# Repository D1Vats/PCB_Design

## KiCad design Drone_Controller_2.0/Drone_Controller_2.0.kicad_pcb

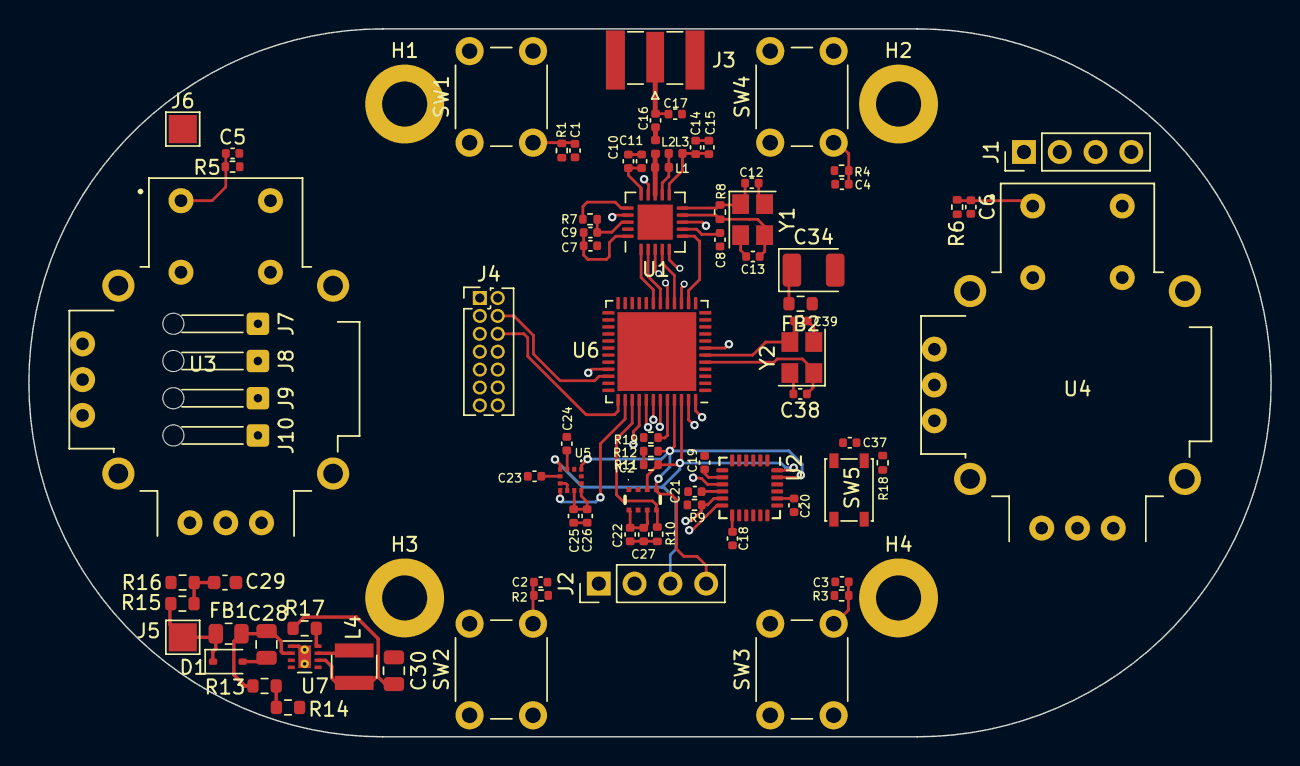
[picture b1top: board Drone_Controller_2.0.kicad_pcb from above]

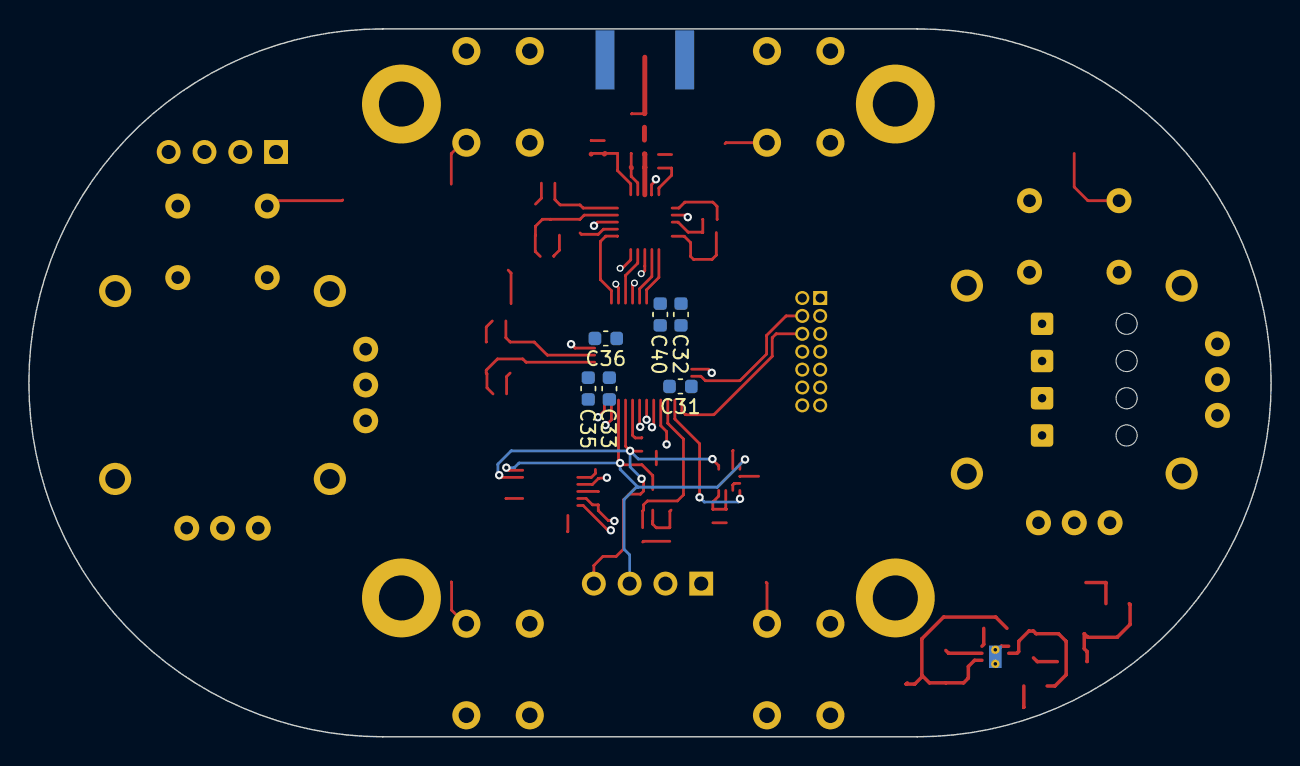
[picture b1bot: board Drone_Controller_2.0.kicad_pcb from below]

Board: 4 copper layers, 88.2 x 50.2 mm, 95 parts (6 on the bottom side), 57 nets.

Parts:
C1, C2, C3, C4, C5, C6: 0.1uf; C_0402_1005Metric
C7: 33nf; C_0402_1005Metric
C8, C24: 10uf; C_0402_1005Metric
C9, C10, C11, C18: 10nf; C_0402_1005Metric
C12, C13, C38, C39: 12pf; C_0402_1005Metric
C14, C20: 2.2nf; C_0402_1005Metric
C15: 4.7p; C_0402_1005Metric
C16: 1p5; C_0402_1005Metric
C17: 1p; C_0402_1005Metric
C19, C21, C22, C25, C26, C27, C37: 100nf; C_0402_1005Metric
C23: 220nf; C_0402_1005Metric
C28: 10uf; C_0805_2012Metric
C29, C36: 10nf; C_0603_1608Metric
C30: 22uf; C_0805_2012Metric
C31, C32, C33: 100nf; C_0603_1608Metric
C34: 1uf; CP_EIA-3528-21_Kemet-B
C35, C40: 4.7uf; C_0603_1608Metric
D1: SD24_SOD323; D_SOD-323
FB1: 120R; R_0805_2012Metric
FB2: 600R@100MHz; R_0603_1608Metric
H1, H2, H3, H4: MountingHole; MountingHole_3.2mm_M3_DIN965_Pad
IC2: DPS310XTSA1
J1, J2: Conn_01x04; PinHeader_1x04_P2.54mm_Vertical
J3: Conn_Coaxial; SMA_Samtec_SMA-J-P-X-ST-EM1_EdgeMount
J4: Conn_ST_STDC14; PinHeader_2x07_P1.27mm_Vertical
J5: V+; TestPoint_Pad_2.0x2.0mm
J6: V-; TestPoint_Pad_2.0x2.0mm
J7, J8, J9, J10: Conn_01x01_Pin; SolderWire-0.1sqmm_1x01_D0.4mm_OD1mm_Relief
L1: 8.2nH; L_0402_1005Metric
L2: 3.9nH; L_0402_1005Metric
L3: 2.7nH; L_0402_1005Metric
L4: VLS252010HBX-2R2M-1; L_Abracon_ASPI-3012S
R1, R2, R3, R4, R5, R6: 3.3k; R_0402_1005Metric
R7: 22k; R_0402_1005Metric
R8: 1M; R_0402_1005Metric
R9: 1k; R_0402_1005Metric
R10: 51k; R_0402_1005Metric
R11, R12: 4.7k; R_0402_1005Metric
R13: 110k; R_0603_1608Metric
R14: 12k; R_0603_1608Metric
R15: 4.7k; R_0603_1608Metric
R16: 1.2k; R_0603_1608Metric
R17: 100k; R_0603_1608Metric
R18, R19: 10k; R_0402_1005Metric
SW1, SW2, SW3, SW4: SW_Push; SW_PUSH_6mm_H4.3mm
SW5: SW_Push; SW_SPST_PTS810
U1: NRF24L01; QFN-20-1EP_4x4mm_P0.5mm_EP2.5x2.5mm
U2: MPU-6050; InvenSense_QFN-24_4x4mm_P0.5mm
U3, U4: COM-09032; XDCR_COM-09032
U5: IIS2MDCTR
U6: STM32F411CEUx; QFN-48-1EP_7x7mm_P0.5mm_EP5.6x5.6mm
U7: TPS62162DSG; WSON-8-1EP_2x2mm_P0.5mm_EP0.9x1.6mm_ThermalVias
Y1, Y2: 16MHz; Crystal_SMD_3225-4Pin_3.2x2.5mm

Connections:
C1: C23.1, U5.5 (C1)
DPS_INT: IC2.5 (SDO), R10.2, U6.39 (PB3)
EN: R13.2, R14.1, U7.3 (EN)
FSYNC: R9.1, U2.11 (FSYNC), U6.41 (PB5)
Filter_V_IN: C28.1, FB1.2, R13.1, U7.2 (VIN)
INT/DRDY: U5.7 (INT/DRDY), U6.38 (PA15)
J_SW1: C5.1, R5.2, U3.B1A (SEL+), U6.25 (PB12)
J_SW2: C6.1, R6.2, U4.B1A (SEL+), U6.10 (PA0)
MPU_I2C_SCL: IC2.4 (SCK), J2.4, R12.2, U2.23 (SCL), U5.1 (SCL/SPC), U6.45 (PB8)
MPU_I2C_SDA: IC2.3 (SDI), J2.3, R11.2, U2.24 (SDA), U5.4 (SDA/SDI/SDO), U6.46 (PB9)
MPU_INT: U2.12 (INT), U6.40 (PB4)
Motor_1: J7.1, U6.29 (PA8)
Motor_2: J8.1, U6.30 (PA9)
Motor_3: J9.1, U6.31 (PA10)
Motor_4: J10.1, U6.32 (PA11)
NRF_!CS: U1.2 (CSN), U6.18 (PB0)
NRF_ANT1: L1.2, L3.2, U1.12 (ANT1)
NRF_ANT2: L1.1, L2.1, U1.13 (ANT2)
NRF_CE: U1.1 (CE), U6.19 (PB1)
NRF_IRQ: U1.6 (IRQ), U6.14 (PA4)
NRF_MISO: U1.5 (MISO), U6.17 (PA7)
NRF_MOSI: U1.4 (MOSI), U6.16 (PA6)
NRF_SCK: U1.3 (SCK), U6.15 (PA5)
NRF_VDD_PA: C14.2, C15.2, L3.1, U1.11 (VDD_PA)
NRF_XC1: C12.1, R8.1, U1.10 (XC1), Y1.1
NRF_XC2: C13.1, R8.2, U1.9 (XC2), Y1.3
NRST: C37.1, J4.12 (~RST), R18.2, SW5.2, U6.7 (NRST)
unnamed: C16.1, L2.2
unnamed: C16.2, C17.2, J3.1 (In)
unnamed: C7.1, U1.19 (DVDD)
unnamed: R7.1, U1.16 (IREF)
unnamed: C20.1, U2.20 (CPOUT)
unnamed: C21.1, U2.10 (REGOUT)
unnamed: R19.2, U6.44 (BOOT0)
unnamed: C40.1, U6.22 (VCAP1)
unnamed: L4.1, U7.7 (SW)
PG: R17.2, U7.8 (PG)
RCC_OSC_IN: C38.1, U6.5 (PH0), Y2.1
RCC_OSC_OUT: C39.1, U6.6 (PH1), Y2.3
STM_VDD: C8.1, C9.1, C10.1, C11.1, C18.1, C19.1, C22.1, C24.1, C25.1, C26.1, C27.1, C30.1, C31.1, C32.1, C33.1, C35.1, FB2.1, IC2.6 (VDDIO), IC2.8 (VDD), J1.1, J2.1, J4.3 (VCC), L4.2, R1.1, R2.1, R3.1, R4.1, R5.1, R6.1, R7.2, R11.1, R12.1, R17.1, R18.1, U1.7 (VDD), U1.15 (VDD), U1.18 (VDD), U2.8 (VLOGIC), U2.13 (VDD), U3.H1 (H+), U3.V1 (V+), U4.H1 (H+), U4.V1 (V+), U5.3 (CS), U5.9 (VDD), U5.10 (VDD_IO), U6.1 (VBAT), U6.24 (VDD), U6.36 (VDD), U6.48 (VDD), U7.6 (VOS)
STM_VSS: C1.2, C2.2, C3.2, C4.2, C5.2, C6.2, C7.2, C8.2, C9.2, C10.2, C11.2, C12.2, C13.2, C14.1, C15.1, C17.1, C18.2, C19.2, C20.2, C21.2, C22.2, C23.2, C24.2, C25.2, C26.2, C27.2, C28.2, C29.2, C30.2, C31.2, C32.2, C33.2, C34.2, C35.2, C36.2, C37.2, C38.2, C39.2, C40.2, D1.2 (A2), IC2.1 (GND_1), IC2.7 (GND_2), J1.4, J2.2, J3.2 (Ext), J4.5 (GND), J4.7 (GND), J4.11 (GNDDetect), J6.1, R9.2, R10.1, R14.2, R16.2, R19.1, SW1.1, SW2.1, SW3.1, SW4.1, SW5.1, U1.8 (VSS), U1.14 (VSS), U1.17 (VSS), U1.20 (VSS), U2.1 (CLKIN), U2.9 (AD0), U2.18 (GND), U3.B2A (SEL-), U3.H3 (H-), U3.V3 (V-), U4.B2A (SEL-), U4.H3 (H-), U4.V3 (V-), U5.6 (GND_1), U5.8 (GND_2), U6.8 (VSSA), U6.23 (VSS), U6.35 (VSS), U6.47 (VSS), U6.49 (VSS), U7.1 (PGND), U7.4 (AGND), U7.5 (FB), U7.9 (PAD), Y1.2, Y1.4, Y2.2, Y2.4
SWCLK: J4.6 (JCLK/SWCLK), U6.37 (PA14)
SWDIO: J4.4 (JTMS/SWDIO), U6.34 (PA13)
SW_1: C1.1, R1.2, SW1.2, U6.21 (PB10)
SW_2: C2.1, R2.2, SW2.2, U6.33 (PA12)
SW_3: C3.1, R3.2, SW3.2, U6.2 (PC13)
SW_4: C4.1, R4.2, SW4.2, U6.11 (PA1)
USART1_RX: J4.13 (VCP_RX), U6.43 (PB7)
USART1_TX: J4.14 (VCP_TX), U6.42 (PB6)
USART2_RX: J1.2, U6.13 (PA3)
USART2_TX: J1.3, U6.12 (PA2)
VDDA: C34.1, C36.1, FB2.2, U6.9 (VDDA)
V_IN: D1.1 (A1), FB1.1, J5.1, R15.1
V_IN_Sense: C29.1, R15.2, R16.1, U6.28 (PB15)
X_2_AXIS: U4.H2 (H), U6.3 (PC14)
Y_1_AXIS: U3.V2 (V), U6.26 (PB13), U6.27 (PB14)
Y_2_AXIS: U4.V2 (V), U6.4 (PC15)

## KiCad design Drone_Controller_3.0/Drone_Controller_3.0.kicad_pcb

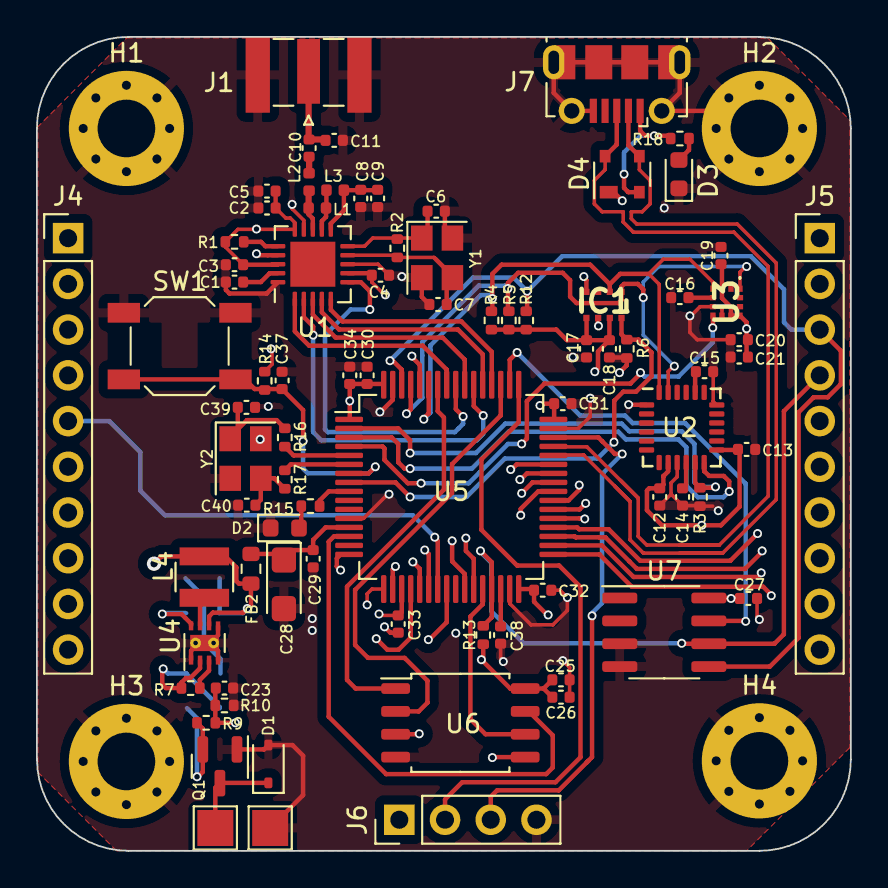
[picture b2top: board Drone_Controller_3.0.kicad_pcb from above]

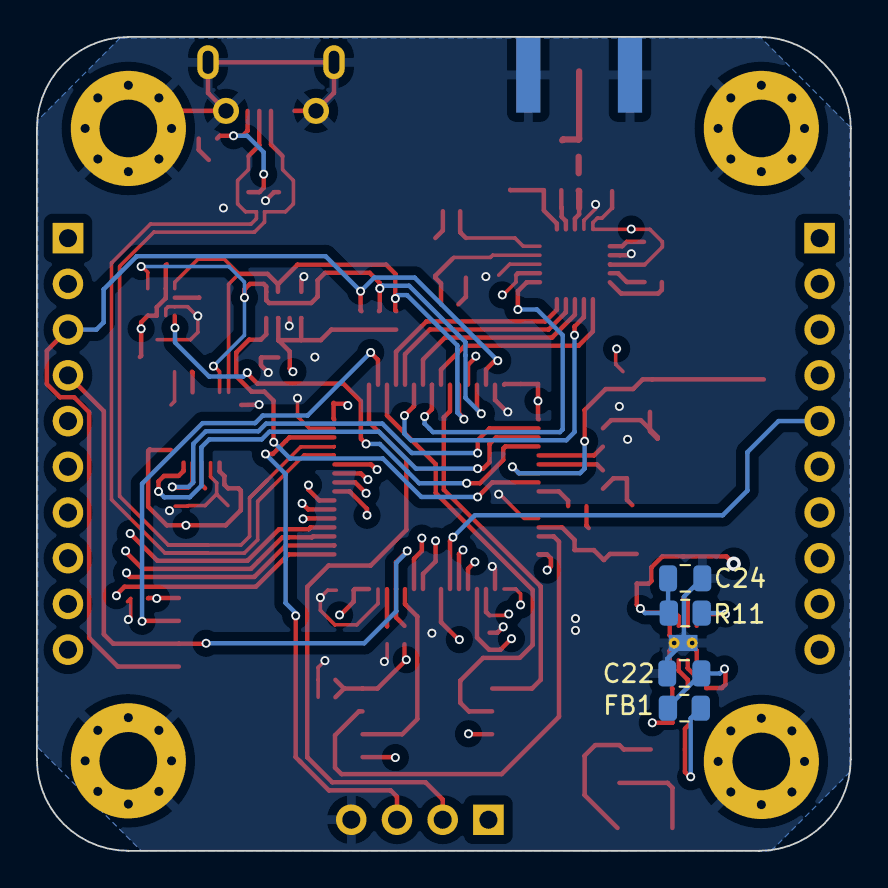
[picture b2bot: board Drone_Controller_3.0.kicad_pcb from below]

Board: 4 copper layers, 45.2 x 45.2 mm, 88 parts (4 on the bottom side), 75 nets.

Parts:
C1: 33nf; C_0402_1005Metric
C2, C19: 10uf; C_0402_1005Metric
C3, C4, C5, C12, C23, C29: 10nf; C_0402_1005Metric
C6, C7, C39, C40: 12pf; C_0402_1005Metric
C8, C15: 2.2nf; C_0402_1005Metric
C9: 4.7p; C_0402_1005Metric
C10: 1p5; C_0402_1005Metric
C11: 1p; C_0402_1005Metric
C13, C14, C17, C18, C20, C21, C30, C31, C32, C33, C37: 100nf; C_0402_1005Metric
C16: 220nf; C_0402_1005Metric
C22: 10uf; C_0805_2012Metric
C24: 22uf; C_0805_2012Metric
C25, C26, C27: 0.1uf; C_0402_1005Metric
C28: 1uf; CP_EIA-3216-18_Kemet-A
C34: 4.7uf; C_0402_1005Metric
C38: 2.2uf; C_0402_1005Metric
D1: SD24_SOD323; D_SOD-323
D2: Green_LED; LED_0603_1608Metric
D3: LED; LED_0603_1608Metric
D4: SP0503BAHT; SOT-143
FB1: 120R; R_0805_2012Metric
FB2: 600R@100MHz; R_0603_1608Metric
H1, H2, H3, H4: MountingHole_Pad; MountingHole_3.2mm_M3_Pad_Via
IC1: DPS310XTSA1
J1: Conn_Coaxial; SMA_Samtec_SMA-J-P-X-ST-EM1_EdgeMount
J2: V+; TestPoint_Pad_2.0x2.0mm
J3: V-; TestPoint_Pad_2.0x2.0mm
J4, J5: Conn_01x10; PinHeader_1x10_P2.54mm_Vertical
J6: Conn_01x04; PinHeader_1x04_P2.54mm_Vertical
J7: USB_B_Micro; USB_Micro-B_Molex-105017-0001
L1: 8.2nH; L_0402_1005Metric
L2: 3.9nH; L_0402_1005Metric
L3: 2.7nH; L_0402_1005Metric
L4: VLS252010HBX-2R2M-1; L_Abracon_ASPI-3012S
Q1: Si2319CDS; SOT-23
R1: 22k; R_0402_1005Metric
R2: 1M; R_0402_1005Metric
R3, R15: 1k; R_0402_1005Metric
R4, R5, R12, R13: 4.7k; R_0402_1005Metric
R6: 51k; R_0402_1005Metric
R7: 110k; R_0402_1005Metric
R9: 47k; R_0402_1005Metric
R10: 12k; R_0402_1005Metric
R11: 100k; R_0805_2012Metric
R14: 10k; R_0402_1005Metric
R16, R17: 0R; R_0402_1005Metric
R18: 2.2k; R_0402_1005Metric
SW1: SW_Push; SW_SPST_SKQG_WithStem
U1: NRF24L01; QFN-20-1EP_4x4mm_P0.5mm_EP2.5x2.5mm
U2: MPU-6050; InvenSense_QFN-24_4x4mm_P0.5mm
U3: IIS2MDCTR
U4: TPS62162DSG; WSON-8-1EP_2x2mm_P0.5mm_EP0.9x1.6mm_ThermalVias
U5: STM32F412RGTx; LQFP-64_10x10mm_P0.5mm
U6: W25Q32JVSS; SOIC-8_5.23x5.23mm_P1.27mm
U7: AT24CS08-SSHM; SOIC-8_3.9x4.9mm_P1.27mm
Y1, Y2: 16MHz; Crystal_SMD_3225-4Pin_3.2x2.5mm

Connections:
3.3V: C2.1, C3.1, C4.1, C5.1, C12.1, C13.1, C17.1, C18.1, C19.1, C20.1, C21.1, C24.1, C25.1, C26.1, C27.1, C30.1, C31.1, C32.1, C33.1, C34.1, FB2.1, IC1.6 (VDDIO), IC1.8 (VDD), J6.1, L4.2, R1.2, R4.1, R5.1, R11.1, R12.1, R13.1, R14.1, U1.7 (VDD), U1.15 (VDD), U1.18 (VDD), U2.8 (VLOGIC), U2.13 (VDD), U3.3 (CS), U3.9 (VDD), U3.10 (VDD_IO), U4.6 (VOS), U5.1 (VBAT), U5.19 (VDD), U5.32 (VDD), U5.48 (VDD), U5.64 (VDD), U6.8 (VCC), U7.8 (VCC)
BOOT0: J4.1, U5.60 (BOOT0)
C1: C16.1, U3.5 (C1)
D+: D4.4 (K), J7.3 (D+), U5.45 (PA12)
D-: D4.3 (K), J7.2 (D-), U5.44 (PA11)
DPS_INT: IC1.5 (SDO), R6.2, U5.8 (PC0)
EEPROM_SCL: J5.4, R13.2, U5.29 (PB10), U7.6 (SCL)
EEPROM_SDA: J5.3, R12.2, U5.62 (PB9), U7.5 (SDA)
EEPROM_WP: U5.50 (PA15), U7.7 (WP)
EN: R7.2, U4.3 (EN)
FLASH_CLK: U5.28 (PB2), U6.6 (CLK)
FLASH_CS: U5.58 (PB6), U6.1 (~CS)
FLASH_IO0: U5.40 (PC9), U6.5 (DI(IO0))
FLASH_IO1: U5.51 (PC10), U6.2 (DO(IO1))
FLASH_IO2: U5.39 (PC8), U6.3 (IO2)
FLASH_IO3: U5.14 (PA0), U6.7 (IO3)
FSYNC: R3.1, U2.11 (FSYNC), U5.2 (PC13)
Filter_V_IN: C22.1, FB1.2, R7.1, U4.2 (VIN)
GND: C1.2, C2.2, C3.2, C4.2, C5.2, C6.2, C7.2, C8.1, C9.1, C11.1, C12.2, C13.2, C14.2, C15.2, C16.2, C17.2, C18.2, C19.2, C20.2, C21.2, C22.2, C23.2, C24.2, C25.2, C26.2, C27.2, C28.2, C29.2, C30.2, C31.2, C32.2, C33.2, C34.2, C37.2, C38.2, C39.2, C40.2, D1.2 (A2), D2.1 (K), D3.1 (K), D4.1 (A), H1.1, H2.1, H3.1, H4.1, IC1.1 (GND_1), IC1.7 (GND_2), J1.2 (Ext), J3.1, J6.4, J7.5 (GND), J7.6 (Shield), Q1.1 (G), R3.2, R6.1, R10.2, SW1.1, U1.8 (VSS), U1.14 (VSS), U1.17 (VSS), U1.20 (VSS), U2.1 (CLKIN), U2.9 (AD0), U2.18 (GND), U3.6 (GND_1), U3.8 (GND_2), U4.1 (PGND), U4.4 (AGND), U4.5 (FB), U4.9 (PAD), U5.12 (VSSA), U5.18 (VSS), U5.31 (VSS), U5.47 (VSS), U5.63 (VSS), U6.4 (GND), U7.3 (A2), U7.4 (GND), Y1.2, Y1.4, Y2.2, Y2.4
INT/DRDY: U3.7 (INT/DRDY), U5.4 (PC15)
MPU_I2C_SCL: IC1.4 (SCK), R5.2, U2.23 (SCL), U3.1 (SCL/SPC), U5.61 (PB8)
MPU_I2C_SDA: IC1.3 (SDI), R4.2, U2.24 (SDA), U3.4 (SDA/SDI/SDO), U5.59 (PB7)
MPU_INT: U2.12 (INT), U5.3 (PC14)
NRF_!CS: U1.2 (CSN), U5.54 (PD2)
NRF_ANT1: L1.2, L3.2, U1.12 (ANT1)
NRF_ANT2: L1.1, L2.1, U1.13 (ANT2)
NRF_CE: U1.1 (CE), U5.57 (PB5)
NRF_IRQ: U1.6 (IRQ), U5.56 (PB4)
NRF_MISO: U1.5 (MISO), U5.52 (PC11)
NRF_MOSI: U1.4 (MOSI), U5.53 (PC12)
NRF_SCK: U1.3 (SCK), U5.55 (PB3)
NRF_VDD_PA: C8.2, C9.2, L3.1, U1.11 (VDD_PA)
NRF_XC1: C6.1, R2.1, U1.10 (XC1), Y1.1
NRF_XC2: C7.1, R2.2, U1.9 (XC2), Y1.3
NRST: C37.1, R14.2, SW1.2, U5.7 (NRST)
unnamed: C10.1, L2.2
unnamed: C39.1, R16.2, Y2.1
unnamed: C40.1, R17.1, Y2.3
unnamed: D1.1 (A1), J2.1, Q1.3 (D)
unnamed: D2.2 (A), R15.2
unnamed: D3.2 (A), R18.1
unnamed: C10.2, C11.2, J1.1 (In)
unnamed: C1.1, U1.19 (DVDD)
unnamed: R1.1, U1.16 (IREF)
unnamed: C15.1, U2.20 (CPOUT)
unnamed: C14.1, U2.10 (REGOUT)
unnamed: L4.1, U4.7 (SW)
unnamed: C38.1, U5.30 (VCAP_1)
PA4: J4.8, U5.20 (PA4)
PA5: J4.7, U5.21 (PA5)
PA8: J4.4, U5.41 (PA8)
PA9: J4.3, U5.42 (PA9)
PA10: J4.2, U5.43 (PA10)
PC6: J5.2, U5.37 (PC6)
PC7: J5.1, U5.38 (PC7)
PG: R11.2, U4.8 (PG)
PWM_1: J4.6, U5.22 (PA6)
PWM_2: J4.5, U5.23 (PA7)
PWM_3: J5.5, U5.26 (PB0)
PWM_4: J5.6, U5.27 (PB1)
RCC_OSC_IN: R16.1, U5.5 (PH0)
RCC_OSC_OUT: R17.2, U5.6 (PH1)
SPI2_MISO: J5.8, U5.35 (PB14)
SPI2_MOSI: J5.7, U5.36 (PB15)
SPI2_NSS: J5.10, U5.33 (PB12)
SPI2_SCK: J5.9, U5.34 (PB13)
SYS_SWCLK: J6.2, U5.49 (PA14)
SYS_SWDIO: J6.3, U5.46 (PA13)
Test_LED: R15.1, U5.9 (PC1)
UART_RX: J4.10, U5.17 (PA3)
UART_TX: J4.9, U5.16 (PA2)
VBUS: D4.2 (K), J7.1 (VBUS), R18.2
VDDA: C28.1, C29.1, FB2.2, U5.13 (VDDA)
V_IN: FB1.1, Q1.2 (S), R9.1
V_IN_Sense: C23.1, R9.2, R10.1, U5.24 (PC4)

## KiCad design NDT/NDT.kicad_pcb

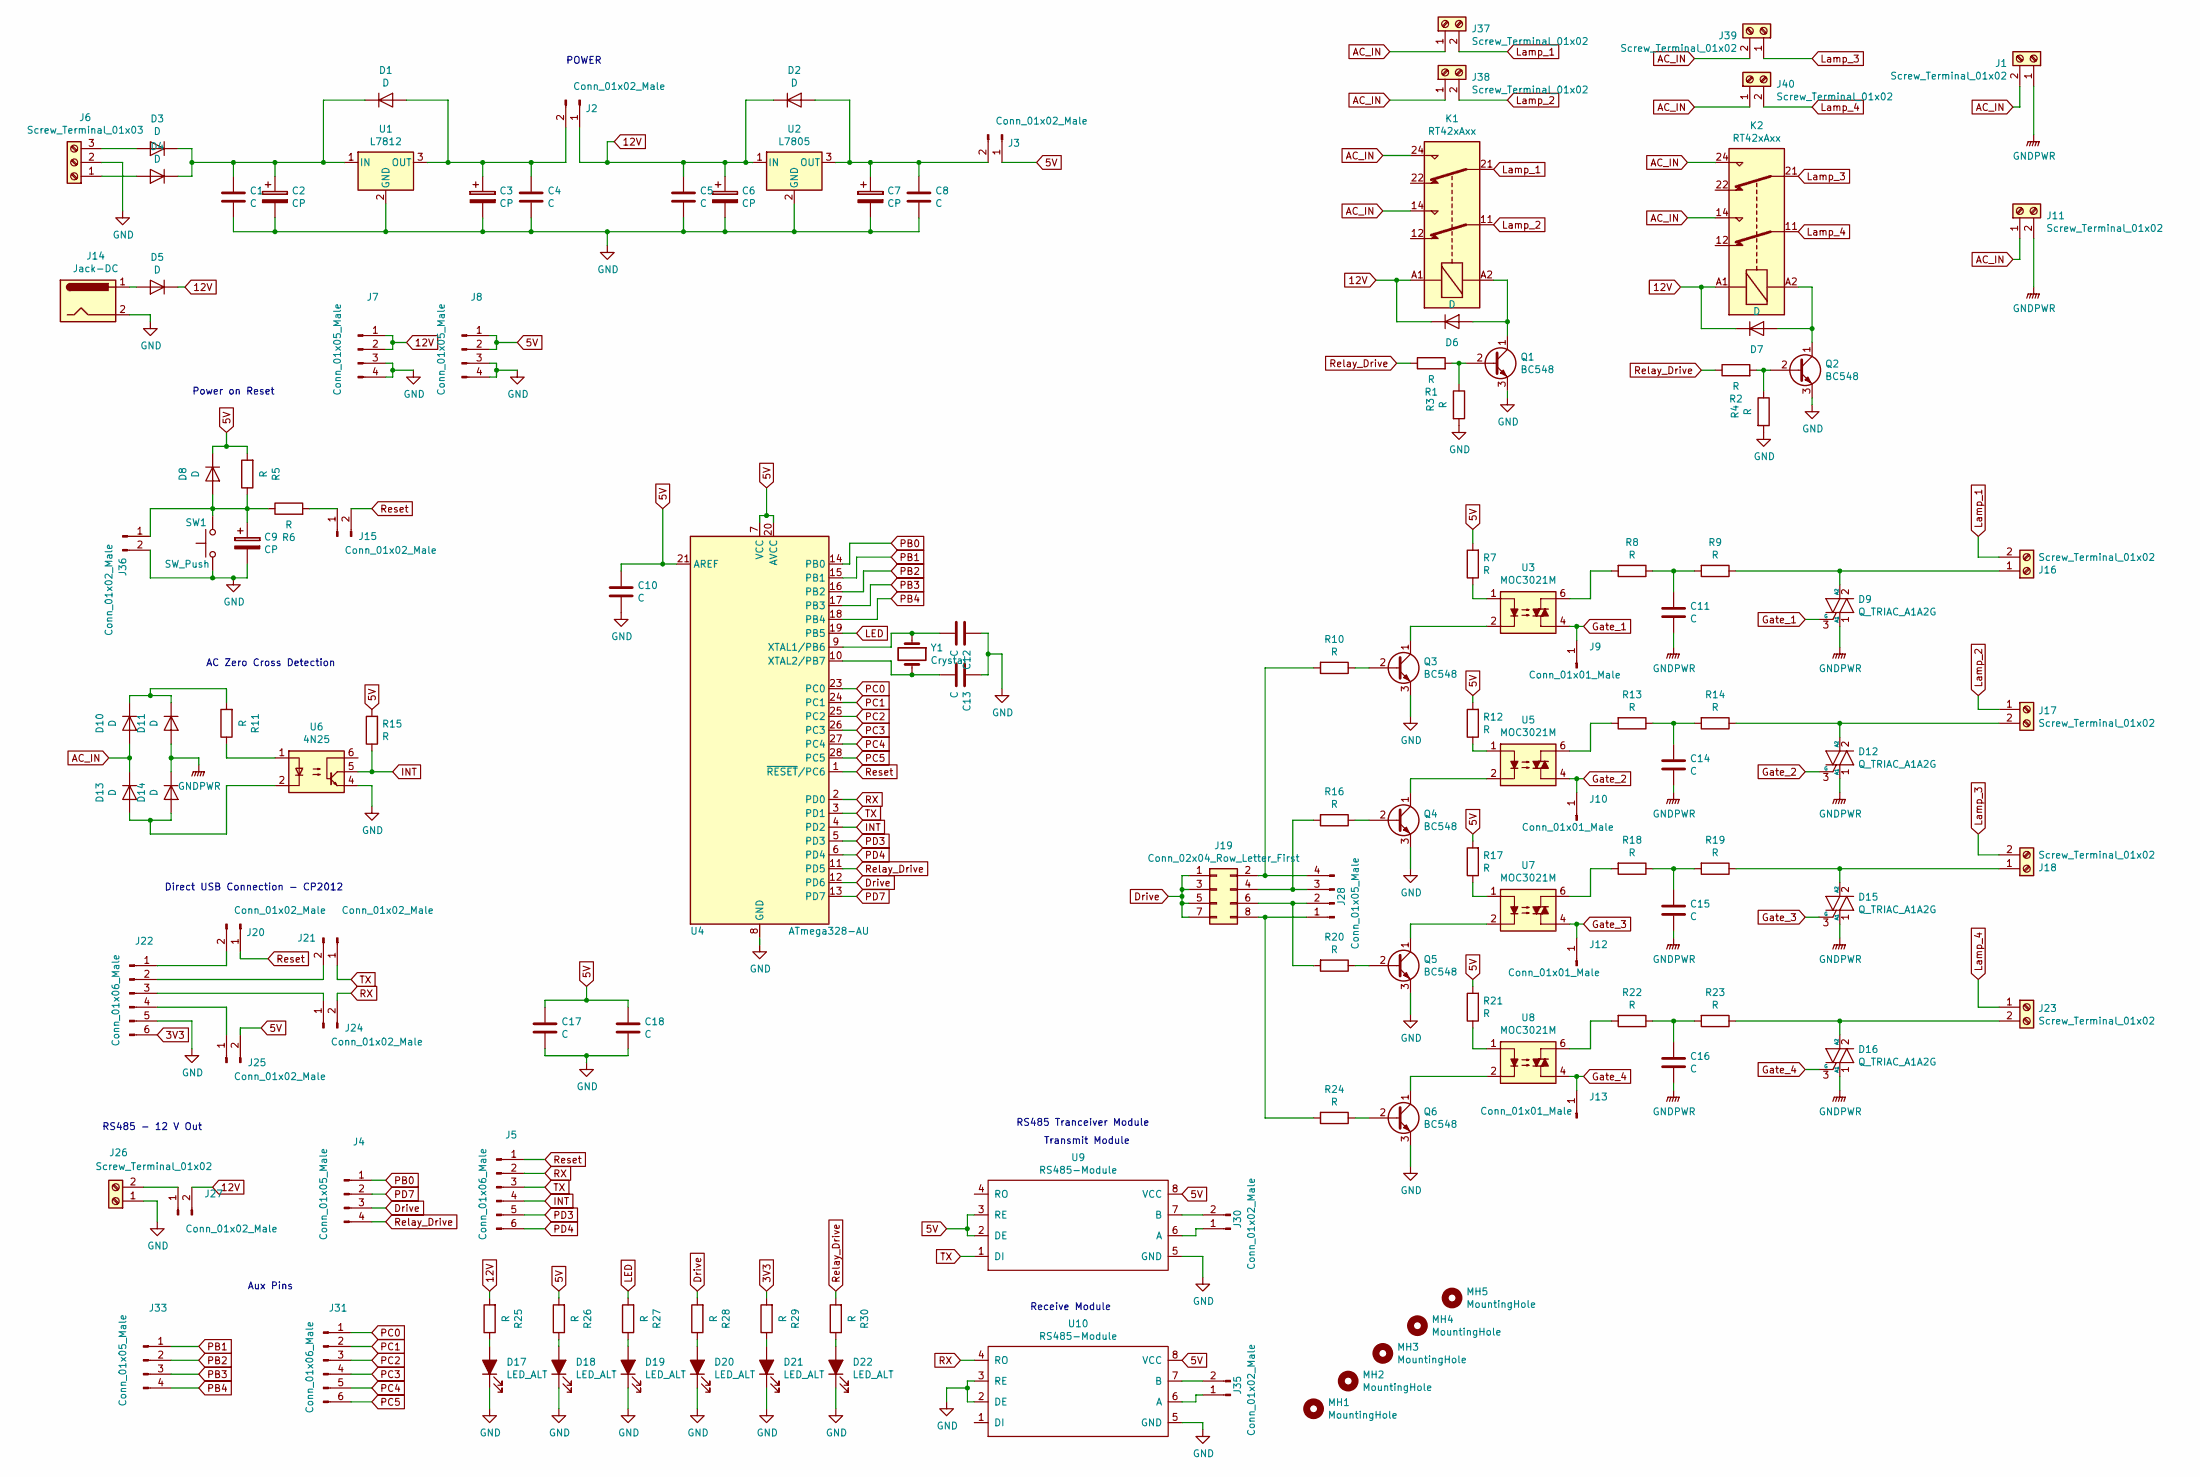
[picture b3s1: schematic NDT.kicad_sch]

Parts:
C1, C4, C5, C8, C10, C17, C18: C; C_Rect_L7.0mm_W2.0mm_P5.00mm
C2, C3, C6, C7: CP; CP_Radial_D10.0mm_P5.00mm
C9: CP; CP_Radial_D5.0mm_P2.50mm
C11, C14, C15, C16: C; C_Axial_L5.1mm_D3.1mm_P15.00mm_Horizontal
C12, C13: C; C_Disc_D3.0mm_W1.6mm_P2.50mm
D1, D2, D3, D4, D5, D6, D7, D8, D10, D11, D13, D14: D; D_5W_P10.16mm_Horizontal
D9, D12, D15, D16: Q_TRIAC_A1A2G; TO-218-3_Vertical
D17, D18, D19, D20, D21, D22: LED_ALT; LED_D3.0mm_Clear
J1, J11, J16, J17, J18, J23, J26, J37, J38, J39, J40: Screw_Terminal_01x02; TerminalBlock_bornier-2_P5.08mm
J2, J3, J15, J20, J21, J24, J25, J27, J30, J35, J36: Conn_01x02_Male; PinHeader_1x02_P2.54mm_Vertical
J4, J7, J8, J28, J33: Conn_01x05_Male; PinHeader_1x04_P2.54mm_Vertical
J5, J22, J31: Conn_01x06_Male; PinHeader_1x06_P2.54mm_Vertical
J6: Screw_Terminal_01x03; TerminalBlock_bornier-3_P5.08mm
J9, J10: Conn_01x01_Male; PinHeader_1x01_P2.54mm_Vertical
J12, J13: Conn_01x01_Male; PinSocket_1x01_P2.54mm_Vertical
J14: Jack-DC; BarrelJack_Horizontal
J19: Conn_02x04_Row_Letter_First; JAE_LY20-8P-DT1_2x04_P2.00mm_Vertical
K1, K2: RT42xAxx; Relay_DPDT_Schrack-RT2-FormC_RM5mm
MH1, MH2, MH3, MH4, MH5: MountingHole; MountingHole_3.2mm_M3
Q1, Q2, Q3, Q4, Q5, Q6: BC548; TO-92_Inline
R1, R2, R3, R4, R5, R6, R7, R10, R11, R12, R15, R16, R17, R20, R21, R24, R25, R26, R27, R28, R29, R30: R; R_Axial_DIN0207_L6.3mm_D2.5mm_P10.16mm_Horizontal
R8, R9, R13, R14, R18, R19, R22, R23: R; R_Axial_DIN0411_L9.9mm_D3.6mm_P15.24mm_Horizontal
SW1: SW_Push; SW_PUSH_6mm_H5mm
U1: L7812; TO-220-3_Vertical
U2: L7805; TO-220-3_Vertical
U3, U5, U7, U8: MOC3021M; DIP-6_W7.62mm_LongPads
U4: ATmega328-AU; DIP-28_W7.62mm_LongPads
U6: 4N25; DIP-6_W7.62mm_LongPads
U9, U10: RS485-Module
Y1: Crystal; Crystal_HC49-4H_Vertical

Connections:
3V3: J22.6, R29.2
5V: C10.1, C17.1, C18.1, D8.1 (K), J3.1, J8.1, J8.2, J25.2, R5.2, R7.2, R12.2, R15.2, R17.2, R21.2, R26.2, U4.7 (VCC), U4.20 (AVCC), U4.21 (AREF), U9.2 (DE), U9.3 (RE), U9.8 (VCC), U10.8 (VCC)
12V: C5.1, C6.1, D2.1 (K), D5.1 (K), D6.1 (K), D7.1 (K), J2.1, J7.1, J7.2, J27.2, K1.A1, K2.A1, R25.2, U2.1 (IN)
AC_IN: D10.2 (A), D13.1 (K), J1.2, J11.1, J37.1, J38.1, J39.2, J40.1, K1.14, K1.24, K2.14, K2.24
Drive: J4.3, J19.1, J19.3, J19.5, J19.7, R28.2, U4.12 (PD6)
GND: C1.2, C2.2, C3.2, C4.2, C5.2, C6.2, C7.2, C8.2, C9.2, C10.2, C12.1, C13.1, C17.2, C18.2, D17.1 (K), D18.1 (K), D19.1 (K), D20.1 (K), D21.1 (K), D22.1 (K), J6.2, J7.3, J7.4, J8.3, J8.4, J14.2, J22.5, J26.1, J36.2, Q1.3 (E), Q2.3 (E), Q3.3 (E), Q4.3 (E), Q5.3 (E), Q6.3 (E), R3.2, R4.2, SW1.1, U1.2 (GND), U2.2 (GND), U4.8 (GND), U4.22 (GND), U6.4, U9.5 (GND), U10.2 (DE), U10.3 (RE), U10.5 (GND)
GNDPWR: C11.2, C14.2, C15.2, C16.2, D9.1 (A1), D11.2 (A), D12.1 (A1), D14.1 (K), D15.1 (A1), D16.1 (A1), J1.1, J11.2
Gate_1: D9.3 (G), J9.1, U3.4
Gate_2: D12.3 (G), J10.1, U5.4
Gate_3: D15.3 (G), J12.1, U7.4
Gate_4: D16.3 (G), J13.1, U8.4
INT: J5.4, R15.1, U4.4 (PD2), U6.5
LED: R27.2, U4.19 (PB5)
Lamp_1: J16.2, J37.2, K1.21
Lamp_2: J17.1, J38.2, K1.11
Lamp_3: J18.2, J39.1, K2.21
Lamp_4: J23.1, J40.2, K2.11
unnamed: C1.1, C2.1, D1.1 (K), D3.1 (K), D4.1 (K), U1.1 (IN)
unnamed: C3.1, C4.1, D1.2 (A), J2.2, U1.3 (OUT)
unnamed: C7.1, C8.1, D2.2 (A), J3.2, U2.3 (OUT)
unnamed: C9.1, D8.2 (A), J36.1, R5.1, R6.1, SW1.2
unnamed: C11.1, R8.1, R9.2
unnamed: C12.2, U4.9 (XTAL1/PB6), Y1.1
unnamed: C13.2, U4.10 (XTAL2/PB7), Y1.2
unnamed: C14.1, R13.1, R14.2
unnamed: C15.1, R18.1, R19.2
unnamed: C16.1, R22.1, R23.2
unnamed: D3.2 (A), J6.3
unnamed: D4.2 (A), J6.1
unnamed: D5.2 (A), J14.1
unnamed: D6.2 (A), K1.A2, Q1.1 (C)
unnamed: D7.2 (A), K2.A2, Q2.1 (C)
unnamed: D9.2 (A2), J16.1, R9.1
unnamed: D10.1 (K), D11.1 (K), R11.2
unnamed: D12.2 (A2), J17.2, R14.1
unnamed: D13.2 (A), D14.2 (A), U6.2
unnamed: D15.2 (A2), J18.1, R19.1
unnamed: D16.2 (A2), J23.2, R23.1
unnamed: D17.2 (A), R25.1
unnamed: D18.2 (A), R26.1
unnamed: D19.2 (A), R27.1
unnamed: D20.2 (A), R28.1
unnamed: D21.2 (A), R29.1
unnamed: D22.2 (A), R30.1
unnamed: J15.1, R6.2
unnamed: J19.2, J28.4, R10.2
unnamed: J19.4, J28.3, R16.2
unnamed: J19.6, J28.2, R20.2
unnamed: J19.8, J28.1, R24.2
unnamed: J20.2, J22.1
unnamed: J21.2, J22.2
unnamed: J22.3, J24.1
unnamed: J22.4, J25.1
unnamed: J26.2, J27.1
unnamed: J30.1, U9.6 (A)
unnamed: J30.2, U9.7 (B)
unnamed: J35.1, U10.6 (A)
unnamed: J35.2, U10.7 (B)
unnamed: Q1.2 (B), R1.2, R3.1
unnamed: Q2.2 (B), R2.2, R4.1
unnamed: Q3.1 (C), U3.2
unnamed: Q3.2 (B), R10.1
unnamed: Q4.1 (C), U5.2
unnamed: Q4.2 (B), R16.1
unnamed: Q5.1 (C), U7.2
unnamed: Q5.2 (B), R20.1
unnamed: Q6.1 (C), U8.2
unnamed: Q6.2 (B), R24.1
unnamed: R7.1, U3.1
unnamed: R8.2, U3.6
unnamed: R11.1, U6.1
unnamed: R12.1, U5.1
unnamed: R13.2, U5.6
unnamed: R17.1, U7.1
unnamed: R18.2, U7.6
unnamed: R21.1, U8.1
unnamed: R22.2, U8.6
PB0: J4.1, U4.14 (PB0)
PB1: J33.1, U4.15 (PB1)
PB2: J33.2, U4.16 (PB2)
PB3: J33.3, U4.17 (PB3)
PB4: J33.4, U4.18 (PB4)
PC0: J31.1, U4.23 (PC0)
PC1: J31.2, U4.24 (PC1)
PC2: J31.3, U4.25 (PC2)
PC3: J31.4, U4.26 (PC3)
PC4: J31.5, U4.27 (PC4)
PC5: J31.6, U4.28 (PC5)
PD3: J5.5, U4.5 (PD3)
PD4: J5.6, U4.6 (PD4)
PD7: J4.2, U4.13 (PD7)
RX: J5.2, J24.2, U4.2 (PD0), U10.4 (RO)
Relay_Drive: J4.4, R1.1, R2.1, R30.2, U4.11 (PD5)
Reset: J5.1, J15.2, J20.1, U4.1 (~RESET/PC6)
TX: J5.3, J21.1, U4.3 (PD1), U9.1 (DI)

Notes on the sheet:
RS485 Tranceiver Module
RS485 - 12 V Out
Direct USB Connection - CP2012
Transmit Module
AC Zero Cross Detection
Power on Reset
Receive Module
POWER
Aux Pins

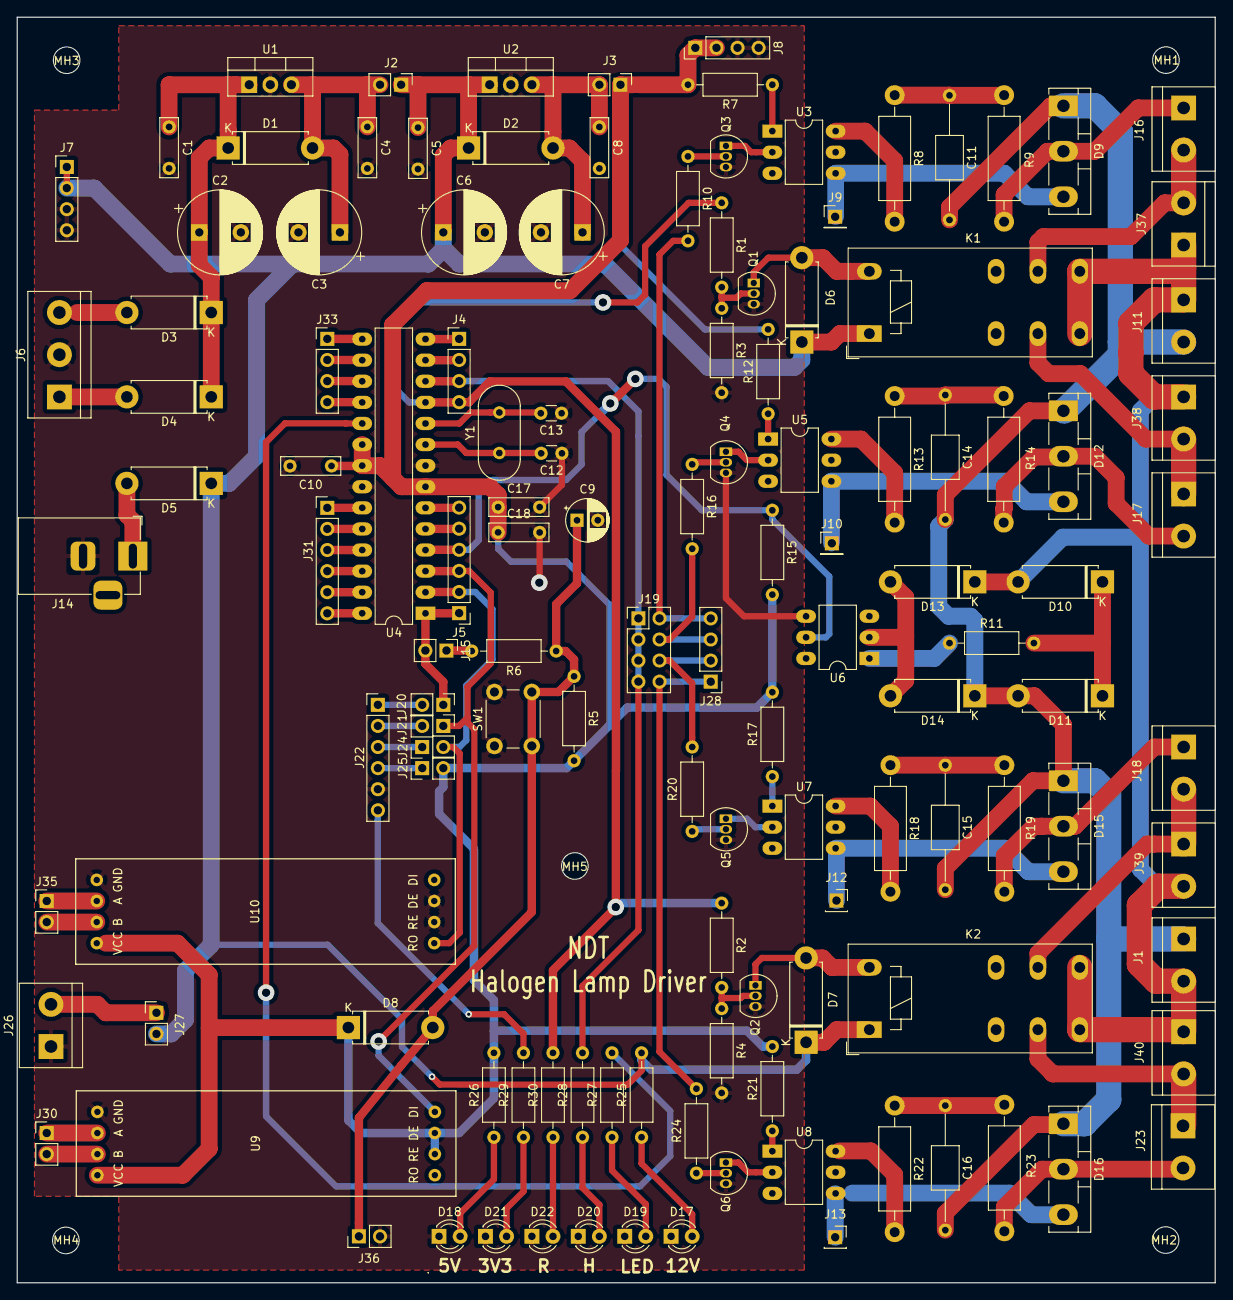
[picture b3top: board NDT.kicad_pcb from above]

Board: 2 copper layers, 144.3 x 152.4 mm, 132 parts (0 on the bottom side), 95 nets.

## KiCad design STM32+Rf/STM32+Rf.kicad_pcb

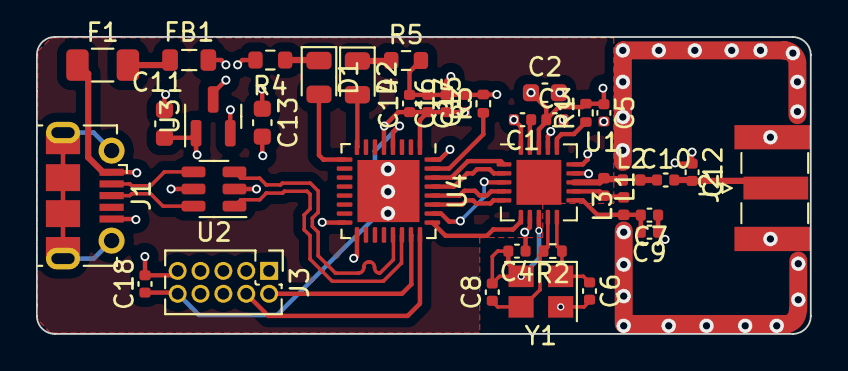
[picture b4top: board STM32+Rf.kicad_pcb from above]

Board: 4 copper layers, 43.0 x 16.5 mm, 38 parts (0 on the bottom side), 32 nets.

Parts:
C1: 33nf; C_0402_1005Metric
C2, C11, C13: 10uf; C_0603_1608Metric
C3, C4, C5: 10nf; C_0402_1005Metric
C6, C8: 12pf; C_0402_1005Metric
C7: 2.2nf; C_0402_1005Metric
C9: 4.7p; C_0402_1005Metric
C10: 1p5; C_0402_1005Metric
C12: 1p; C_0402_1005Metric
C14: 1uf; C_0402_1005Metric
C15, C16, C17, C18: 100nf; C_0402_1005Metric
D1, D2: LED; LED_0805_2012Metric
F1: 100mA; Fuse_1206_3216Metric
FB1: 100 @ 100MHZ; L_0805_2012Metric
J1: USB_B_Micro; USB_Micro-B_Molex-105017-0001
J2: Conn_Coaxial; SMA_Samtec_SMA-J-P-X-ST-EM1_EdgeMount
J3: Conn_02x05_Odd_Even; PinHeader_2x05_P1.27mm_Vertical
L1: 8.2nH; L_0402_1005Metric
L2: 3.9nH; L_0402_1005Metric
L3: 2.7nH; L_0402_1005Metric
R1: 22k; R_0402_1005Metric
R2: 1M; R_0402_1005Metric
R3: 1ok; R_0402_1005Metric
R4, R5: 2k2; R_0603_1608Metric
U1: NRF24L01; QFN-20-1EP_4x4mm_P0.5mm_EP2.5x2.5mm
U2: USBLC6-2SC6; SOT-23-6
U3: XC6206PxxxMR; SOT-23
U4: STM32L432KBUx; QFN-32-1EP_5x5mm_P0.5mm_EP3.45x3.45mm
Y1: 16MHz; Crystal_SMD_3225-4Pin_3.2x2.5mm

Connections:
3.3V_Out: C2.1, C3.1, C4.1, C5.1, C13.1, C14.1, C15.1, C16.1, C17.1, J3.1, R1.2, U1.7 (VDD), U1.15 (VDD), U1.18 (VDD), U3.2 (VO), U4.1 (VDD), U4.5 (VDDA), U4.17 (VDD)
5V_USB: F1.1, J1.1 (VBUS), U2.5 (VBUS)
GND: C1.2, C2.2, C3.2, C4.2, C5.2, C6.2, C7.1, C8.2, C9.1, C11.2, C12.1, C13.2, C14.2, C15.2, C16.2, C17.2, C18.2, J1.5 (GND), J2.2 (Ext), J3.3, J3.5, J3.9, R3.2, R4.2, R5.2, U1.8 (VSS), U1.14 (VSS), U1.17 (VSS), U1.20 (VSS), U2.2 (GND), U3.1 (GND), U4.16 (VSS), U4.32 (VSS), U4.33 (VSS), Y1.2, Y1.4
NRF_ANT1: L1.2, L3.2, U1.12 (ANT1)
NRF_ANT2: L1.1, L2.1, U1.13 (ANT2)
NRF_CE: U1.1 (CE), U4.30 (PB7)
NRF_IRQ: U1.6 (IRQ), U4.25 (PA15)
NRF_VDD_PA: C7.2, C9.2, L3.1, U1.11 (VDD_PA)
NRF_XC1: C6.1, R2.1, U1.10 (XC1), Y1.1
NRF_XC2: C8.1, R2.2, U1.9 (XC2), Y1.3
NRST: C18.1, J3.10, U4.4 (NRST)
unnamed: C1.1, U1.19 (DVDD)
unnamed: C10.1, L2.2
unnamed: C10.2, C12.2, J2.1 (In)
unnamed: C11.1, FB1.2, U3.3 (VI)
unnamed: D1.1 (K), R4.1
unnamed: D1.2 (A), U4.9 (PA3)
unnamed: D2.1 (K), R5.1
unnamed: D2.2 (A), U4.8 (PA2)
unnamed: F1.2, FB1.1
unnamed: R1.1, U1.16 (IREF)
unnamed: R3.1, U4.31 (PH3)
SPI3_!CS: U1.2 (CSN), U4.29 (PB6)
SPI3_MISO: U1.5 (MISO), U4.27 (PB4)
SPI3_MOSI: U1.4 (MOSI), U4.28 (PB5)
SPI3_SCK: U1.3 (SCK), U4.26 (PB3)
SWCLK: J3.4, U4.24 (PA14)
SWDIO: J3.2, U4.23 (PA13)
USB_D+: U2.1 (I/O1), U4.22 (PA12)
USB_D-: U2.3 (I/O2), U4.21 (PA11)
USB_ESD_D+: J1.3 (D+), U2.6 (I/O1)
USB_ESD_D-: J1.2 (D-), U2.4 (I/O2)
